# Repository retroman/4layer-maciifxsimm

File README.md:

# 4-Layer Macintosh IIfx 16 MB SIMM

This repository contains a PCB layout for a 16MB SIMM to be used in
the Macintosh IIfx system.  The SIMM is a proprietary, 8 bit wide
proprietary type with 64 pins. It is based on the two-layer design,
https://github.com/hanshuebner/maciifxsimm
by Hans Hübner.

Notable changes:
* A ground plane and a partial power plane has been added.
* Signals are not routed between pins to ease hand soldering.
* Capacitors were relocated directly underneath the chips to improve bypassing.
* The ground plane was extended to some of the pins that are unused by the IIfx to optionally improve signal quality.

The design has been tested with 128MB of HM5116100AS7 chips in a repaired battery-damaged IIfx using the Snooper memory test.
Maximum overclock was 60 MHz with 5.30V, and 57 MHz with 4.97V -- the same as a factory-assembled 8MB 70ns SIMM set.

## Fabrication Notes
A set of 10 test PCBs were manufactured by JLCPCB on 2025-08-16 using the following order parameters:
Base Material:	FR-4
Layers:	4
Dimension:	97.8 mm* 22.2 mm
Delivery Format:	Single PCB
PCB Thickness:	1.2mm
Specify Stackup:	no No requirement
PCB Color:	Green
Silkscreen:	White
Via Covering:	Untented
Surface Finish:	HASL(with lead)
Deburring/Edge rounding:	Yes
Outer Copper Weight:	1 oz
Inner Copper Weight:	1 oz
Gold Fingers:	No
Electrical Test:	Flying Probe Fully Test
Castellated Holes:	no
Press-Fit Hole:	No
Edge Plating:	No
Mark on PCB	Remove Mark
Blind Slot:	No
Min via hole size/diameter:	0.3mm/(0.4/0.45mm)
4-Wire Kelvin Test:	No
Appearance Quality:	IPC Class 2 Standard
Silkscreen Technology:	Ink-jet/Screen Printing Silkscreen
Board Outline Tolerance:	±0.2mm(Regular)
Countersink Hole:	No
Backdrill:	No
Total Cost: US$87.53

With a 1.2mm board thickness and 1oz inner copper with HASL finish, the SIMMs fit well into the sockets without additional solder.

The chip spacing is enough to fit a small iron for hand soldering.
The capacitors were soldered first, then a thick coating of solder with rosin flux was placed on each pad.
The corners of the chips were soldered, then a hot plate was used to reflow the rest of the pins.

## License

This work is licensed under a Creative Commons Attribution-ShareAlike
4.0 International License. See
[https://creativecommons.org/licenses/by-sa/4.0/](https://creativecommons.org/licenses/by-sa/4.0/).

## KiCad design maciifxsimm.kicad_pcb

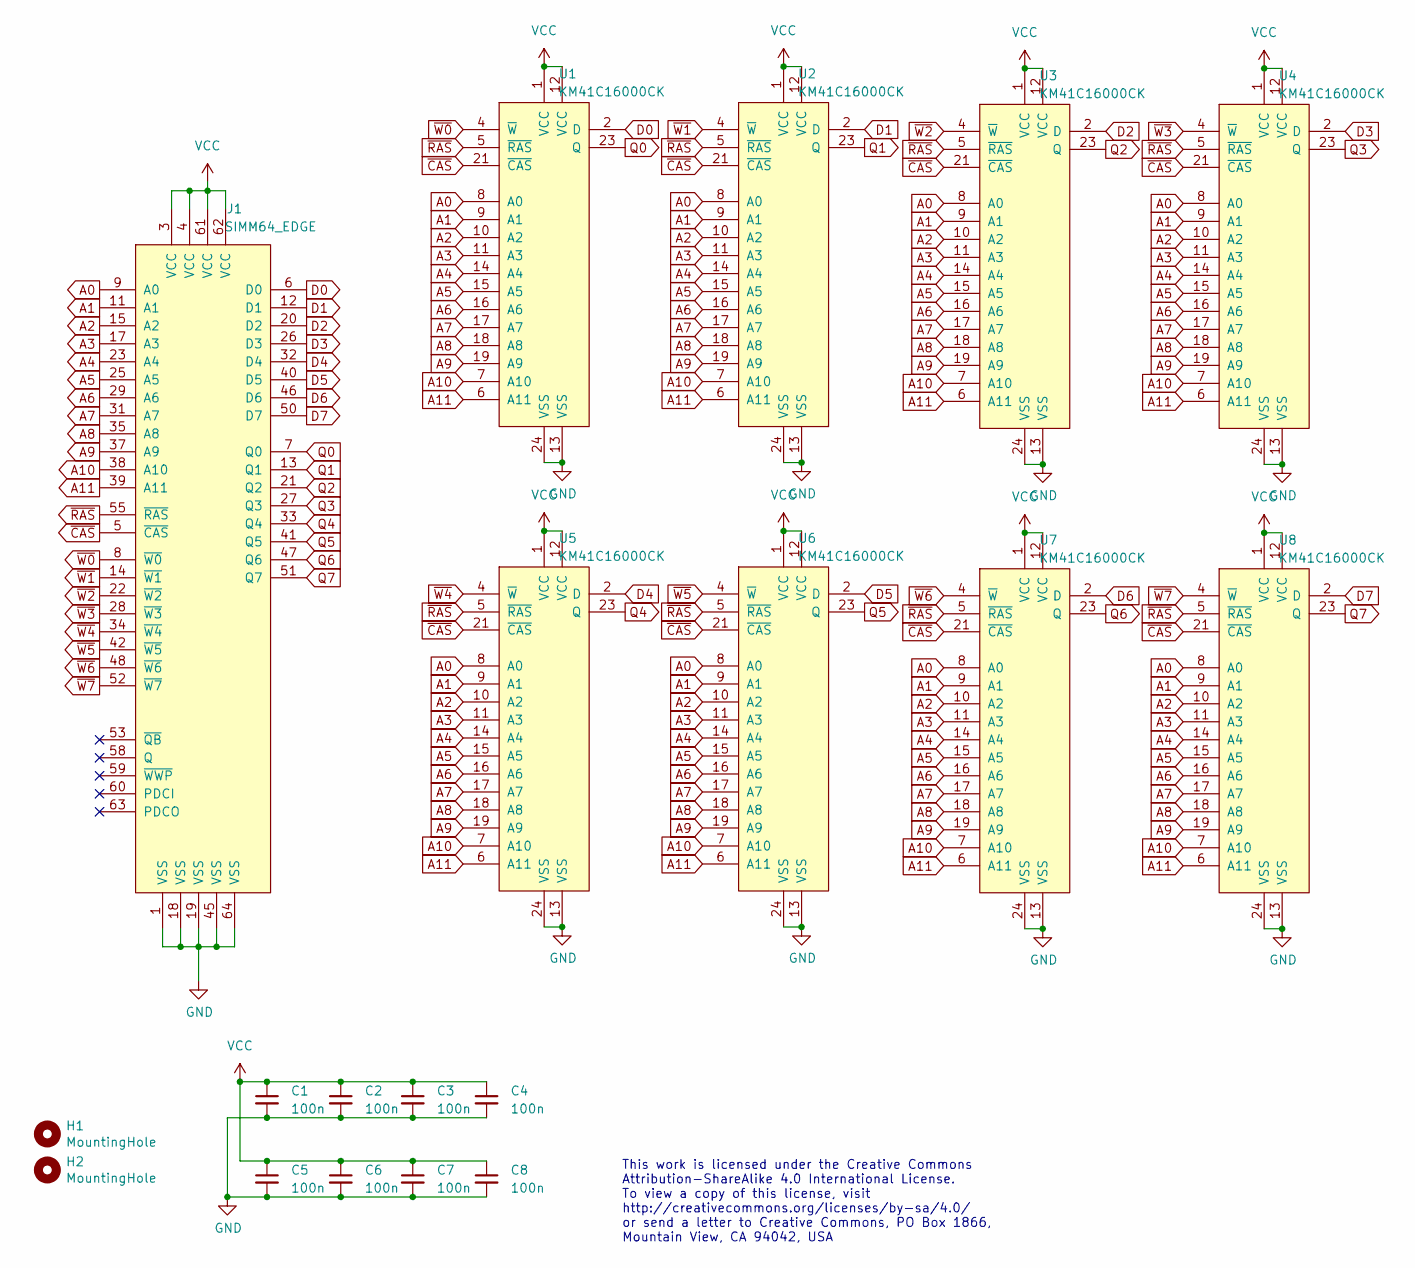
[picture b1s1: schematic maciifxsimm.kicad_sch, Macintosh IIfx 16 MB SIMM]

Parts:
C1, C2, C3, C4, C5, C6, C7, C8: 100n; C_0603_1608Metric_Pad1.08x0.95mm_HandSolder
H1, H2: MountingHole; MH_125
J1: SIMM64_EDGE; EDGE_SIMM_64_127
U1, U2, U3, U4, U5, U6, U7, U8: KM41C16000CK; SOJ127P851X356-20_alt

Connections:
A0: J1.9 (A0), U1.8 (A0), U2.8 (A0), U3.8 (A0), U4.8 (A0), U5.8 (A0), U6.8 (A0), U7.8 (A0), U8.8 (A0)
A1: J1.11 (A1), U1.9 (A1), U2.9 (A1), U3.9 (A1), U4.9 (A1), U5.9 (A1), U6.9 (A1), U7.9 (A1), U8.9 (A1)
A2: J1.15 (A2), U1.10 (A2), U2.10 (A2), U3.10 (A2), U4.10 (A2), U5.10 (A2), U6.10 (A2), U7.10 (A2), U8.10 (A2)
A3: J1.17 (A3), U1.11 (A3), U2.11 (A3), U3.11 (A3), U4.11 (A3), U5.11 (A3), U6.11 (A3), U7.11 (A3), U8.11 (A3)
A4: J1.23 (A4), U1.14 (A4), U2.14 (A4), U3.14 (A4), U4.14 (A4), U5.14 (A4), U6.14 (A4), U7.14 (A4), U8.14 (A4)
A5: J1.25 (A5), U1.15 (A5), U2.15 (A5), U3.15 (A5), U4.15 (A5), U5.15 (A5), U6.15 (A5), U7.15 (A5), U8.15 (A5)
A6: J1.29 (A6), U1.16 (A6), U2.16 (A6), U3.16 (A6), U4.16 (A6), U5.16 (A6), U6.16 (A6), U7.16 (A6), U8.16 (A6)
A7: J1.31 (A7), U1.17 (A7), U2.17 (A7), U3.17 (A7), U4.17 (A7), U5.17 (A7), U6.17 (A7), U7.17 (A7), U8.17 (A7)
A8: J1.35 (A8), U1.18 (A8), U2.18 (A8), U3.18 (A8), U4.18 (A8), U5.18 (A8), U6.18 (A8), U7.18 (A8), U8.18 (A8)
A9: J1.37 (A9), U1.19 (A9), U2.19 (A9), U3.19 (A9), U4.19 (A9), U5.19 (A9), U6.19 (A9), U7.19 (A9), U8.19 (A9)
A10: J1.38 (A10), U1.7 (A10), U2.7 (A10), U3.7 (A10), U4.7 (A10), U5.7 (A10), U6.7 (A10), U7.7 (A10), U8.7 (A10)
A11: J1.39 (A11), U1.6 (A11), U2.6 (A11), U3.6 (A11), U4.6 (A11), U5.6 (A11), U6.6 (A11), U7.6 (A11), U8.6 (A11)
D0: J1.6 (D0), U1.2 (D)
D1: J1.12 (D1), U2.2 (D)
D2: J1.20 (D2), U3.2 (D)
D3: J1.26 (D3), U4.2 (D)
D4: J1.32 (D4), U5.2 (D)
D5: J1.40 (D5), U6.2 (D)
D6: J1.46 (D6), U7.2 (D)
D7: J1.50 (D7), U8.2 (D)
GND: C1.2, C2.2, C3.2, C4.2, C5.2, C6.2, C7.2, C8.2, J1.1 (VSS), J1.10, J1.18 (VSS), J1.19 (VSS), J1.24, J1.30, J1.36, J1.45 (VSS), J1.49, J1.54, J1.56, J1.64 (VSS), U1.13 (VSS), U1.24 (VSS), U2.13 (VSS), U2.24 (VSS), U3.13 (VSS), U3.24 (VSS), U4.13 (VSS), U4.24 (VSS), U5.13 (VSS), U5.24 (VSS), U6.13 (VSS), U6.24 (VSS), U7.13 (VSS), U7.24 (VSS), U8.13 (VSS), U8.24 (VSS)
Q0: J1.7 (Q0), U1.23 (Q)
Q1: J1.13 (Q1), U2.23 (Q)
Q2: J1.21 (Q2), U3.23 (Q)
Q3: J1.27 (Q3), U4.23 (Q)
Q4: J1.33 (Q4), U5.23 (Q)
Q5: J1.41 (Q5), U6.23 (Q)
Q6: J1.47 (Q6), U7.23 (Q)
Q7: J1.51 (Q7), U8.23 (Q)
VCC: C1.1, C2.1, C3.1, C4.1, C5.1, C6.1, C7.1, C8.1, J1.3 (VCC), J1.4 (VCC), J1.61 (VCC), J1.62 (VCC), U1.1 (VCC), U1.12 (VCC), U2.1 (VCC), U2.12 (VCC), U3.1 (VCC), U3.12 (VCC), U4.1 (VCC), U4.12 (VCC), U5.1 (VCC), U5.12 (VCC), U6.1 (VCC), U6.12 (VCC), U7.1 (VCC), U7.12 (VCC), U8.1 (VCC), U8.12 (VCC)
~CAS: J1.5 (~CAS), U1.21 (~CAS), U2.21 (~CAS), U3.21 (~CAS), U4.21 (~CAS), U5.21 (~CAS), U6.21 (~CAS), U7.21 (~CAS), U8.21 (~CAS)
~RAS: J1.55 (~RAS), U1.5 (~RAS), U2.5 (~RAS), U3.5 (~RAS), U4.5 (~RAS), U5.5 (~RAS), U6.5 (~RAS), U7.5 (~RAS), U8.5 (~RAS)
~W0: J1.8 (~W0), U1.4 (~W)
~W1: J1.14 (~W1), U2.4 (~W)
~W2: J1.22 (~W2), U3.4 (~W)
~W3: J1.28 (~W3), U4.4 (~W)
~W4: J1.34 (~W4), U5.4 (~W)
~W5: J1.42 (~W5), U6.4 (~W)
~W6: J1.48 (~W6), U7.4 (~W)
~W7: J1.52 (~W7), U8.4 (~W)

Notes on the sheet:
This work is licensed under the Creative Commons Attribution-ShareAlike 4.0 International License. To view a copy of this license, visit http://creativecommons.org/licenses/by-sa/4.0/ or send a letter to Creative Commons, PO Box 1866, Mountain View, CA 94042, USA

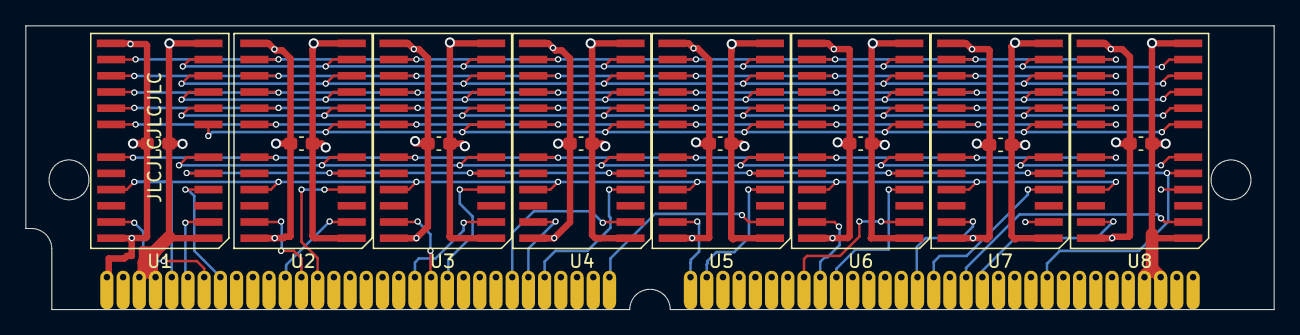
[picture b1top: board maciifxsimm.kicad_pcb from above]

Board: 4 copper layers, 97.8 x 22.2 mm, 19 parts (0 on the bottom side), 40 nets.

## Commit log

2023-09-15 rename and clean up for KiCAD 7
2023-09-15 add v1 gerbers
2023-09-15 v1 sent to fab
2023-09-15 add KM41C16000CK data sheet
2023-10-08 fix issues found in the first run
2023-11-09 add picture
2025-10-22 Add files via upload
    4-layer modifications
2025-10-23 add 4layer images
2025-10-23 readme for 4-layer design
